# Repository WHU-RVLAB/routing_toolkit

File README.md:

# routing toolkit

## Introduction

## Installation
development installation (direct link to the source code):
```bash
pip install -e .
```
installation (build packege and install it to python site-packages):
```bash
pip install .
```

## Running
routing pcb from kicad:
```bash
python src/rtools/main.py [--kicad_pcb <filepath>] [--kicad_pro <filepath>] [--save_file <filename>]
```

## Thanks to
Code used in this project is based on the following repositories: 

### Parser:
- https://github.com/mvnmgrx/kiutils

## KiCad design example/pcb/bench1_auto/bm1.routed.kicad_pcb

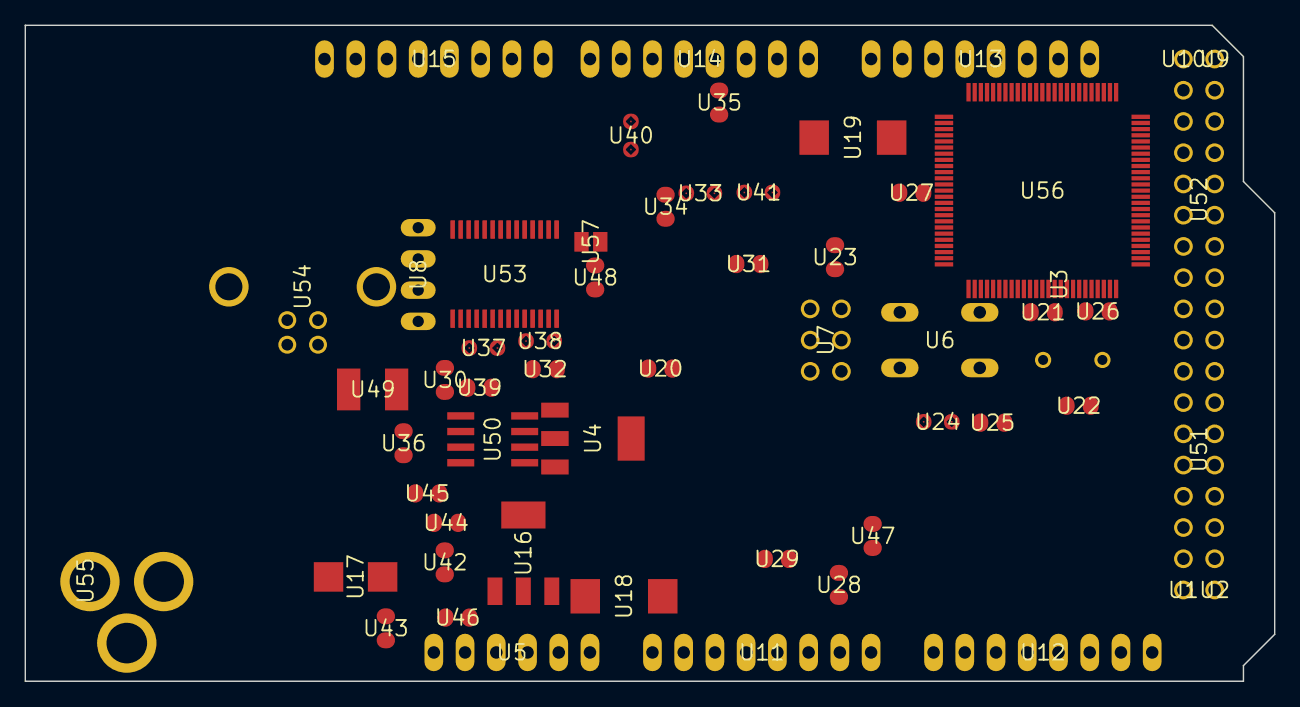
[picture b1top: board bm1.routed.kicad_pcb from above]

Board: 2 copper layers, 101.6 x 53.3 mm, 57 parts (0 on the bottom side), 99 nets, no tracks yet.

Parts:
U1, U2, U9, U10: 1X01
U3: HC49_S
U4, U16: SOT223
U5: 1X06
U6: B3F-10XX
U7: 2X03
U8: JP4
U11, U12, U13, U14, U15: 1X08
U17: SMB
U18, U19: SMC_D
U20, U21, U22, U23, U28, U29, U30, U31, U35, U36, U43, U44, U46, U48: C0805RND
U24, U33, U37, U38: 0805RND
U25, U26, U27, U32, U34, U39, U42, U45, U47: R0805RND
U40, U41: RCL_0805RND
U49: L1812
U50: SO08
U51, U52: 2X08
U53: SSOP28
U54: PN61729
U55: DC-21MM
U56: TQFP100
U57: SJ

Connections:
+3V3: U5.2, U30.2, U50.2, U53.17
+5V: U4.3, U5.3, U7.2, U9.1, U10.1, U16.2, U16.4, U19.+, U20.1, U23.1, U25.1, U26.1, U27.1, U28.1, U29.2, U31.1, U32.2, U39.2, U47.2, U50.8, U53.4, U53.19, U53.20, U56.10, U56.31, U56.61, U56.80, U56.100
ADC0: U11.1, U56.97
ADC1: U11.2, U56.96
ADC2: U11.3, U56.95
ADC3: U11.4, U56.94
ADC4: U11.5, U56.93
ADC5: U11.6, U56.92
ADC6: U11.7, U56.91
ADC7: U11.8, U56.90
ADC8: U12.1, U56.89
ADC9: U12.2, U56.88
ADC10: U12.3, U56.87
ADC11: U12.4, U56.86
ADC12: U12.5, U56.85
ADC13: U12.6, U56.84
ADC14: U12.7, U56.83
ADC15: U12.8, U56.82
AREF: U15.8, U35.1, U56.98
CMP: U42.1, U44.2, U45.2, U50.3
CTS: U8.1, U53.11
D+: U53.15, U54.3
D-: U53.16, U54.2
DCD: U8.3, U53.10
DSR: U8.2, U53.9
DTR: U48.1, U53.2, U57.1, U57.2
GATE_CMD: U4.1, U50.6, U50.7
GND: U1.1, U2.1, U5.4, U5.5, U6.1, U6.2, U7.6, U15.7, U16.1, U18.-, U19.-, U20.2, U21.1, U22.1, U23.2, U24.P$2, U28.2, U29.1, U30.1, U31.2, U33.P$2, U35.2, U36.2, U43.2, U44.1, U45.1, U46.2, U50.4, U53.7, U53.18, U53.21, U53.25, U53.26, U54.4, U54.P$1, U54.P$2, U55.1, U55.3, U56.11, U56.32, U56.62, U56.81, U56.99
M8RXD: U40.P$1, U53.1
M8TXD: U41.P$1, U53.5
unnamed: U33.P$1, U34.2
unnamed: U24.P$1, U25.2
unnamed: U50.1, U50.5
unnamed: U3.1, U21.2, U56.34
unnamed: U3.2, U22.2, U56.33
unnamed: U38.P$2, U53.23
unnamed: U37.P$2, U53.22
unnamed: U32.1, U38.P$1
unnamed: U37.P$1, U39.1
unnamed: U49.2, U54.1
PA0: U52.16, U56.78
PA1: U52.15, U56.77
PA2: U52.14, U56.76
PA3: U52.13, U56.75
PA4: U52.12, U56.74
PA5: U52.11, U56.73
PA6: U52.10, U56.72
PA7: U52.9, U56.71
PB0: U51.1, U56.19
PB1: U7.3, U51.2, U56.20
PB2: U7.4, U51.3, U56.21
PB3: U7.1, U51.4, U56.22
PB4: U15.3, U56.23
PB5: U15.4, U56.24
PB6: U15.5, U56.25
PB7: U15.6, U34.1, U56.26
PC0: U52.1, U56.53
PC1: U52.2, U56.54
PC2: U52.3, U56.55
PC3: U52.4, U56.56
PC4: U52.5, U56.57
PC5: U52.6, U56.58
PC6: U52.7, U56.59
PC7: U52.8, U56.60
PD7: U51.16, U56.50
PE0: U14.1, U40.P$2, U56.2
PE1: U14.2, U41.P$2, U56.3
PE3: U14.6, U56.5
PE4: U14.3, U56.6
PE5: U14.4, U56.7
PG0: U51.13, U56.51
PG1: U51.14, U56.52
PG2: U51.15, U56.70
PG5: U14.5, U56.1
PH3: U14.7, U56.15
PH4: U14.8, U56.16
PH5: U15.1, U56.17
PH6: U15.2, U56.18
PL0: U51.5, U56.35
PL1: U51.6, U56.36
PL2: U51.7, U56.37
PL3: U51.8, U56.38
PL4: U51.9, U56.39
PL5: U51.10, U56.40
PL6: U51.11, U56.41
PL7: U51.12, U56.42
PWRIN: U17.A, U55.2
RESET: U5.1, U6.3, U6.4, U7.5, U46.1, U47.1, U48.2, U56.30
RI: U8.4, U53.6
RXD1: U13.3, U56.45
RXD2: U13.5, U56.12
RXD3: U13.7, U56.63
SCL: U13.1, U26.2, U56.43
SDA: U13.2, U27.2, U56.44
TXD1: U13.4, U56.46
TXD2: U13.6, U56.13
TXD3: U13.8, U56.64
USBVCC: U4.2, U36.1, U49.1
VIN: U5.6, U16.3, U17.C, U18.+, U42.2, U43.1

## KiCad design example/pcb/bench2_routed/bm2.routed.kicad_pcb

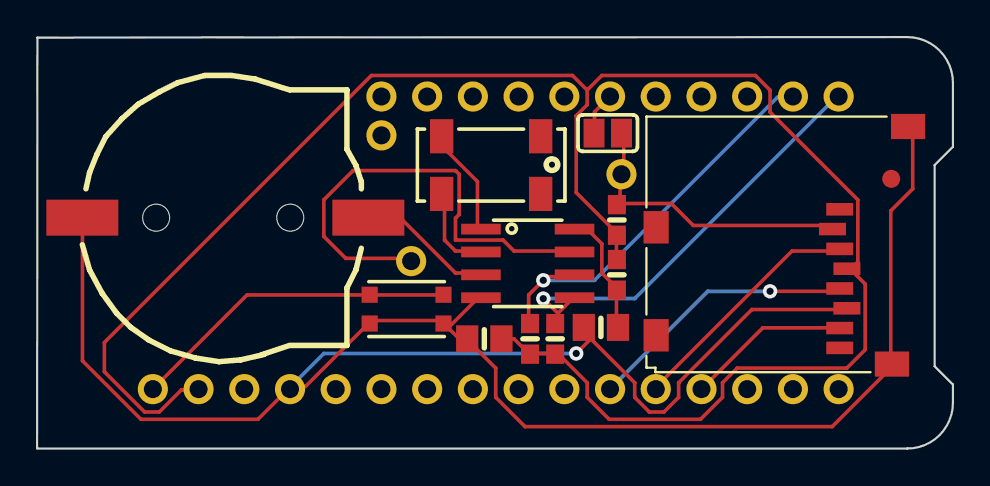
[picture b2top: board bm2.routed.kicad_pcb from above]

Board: 2 copper layers, 50.9 x 22.9 mm, 18 parts (0 on the bottom side), 15 nets.

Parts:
B1: cr1220; CR1220-2
C1, C2: 10uF; 0805-NO
FID1: FIDUCIAL_1MM
IC1: PCF8523T; SOIC8_150MIL
INT1: 1X01_ROUND
JP1: 1X11_ROUND
JP2: 1X16_ROUND
JP3: 1X01_ROUND
R1, R2: 10K; 0603-NO
R3: 100K; 0603-NO
R4: 1K; 0603-NO
SDCS: 1X01_ROUND
SJ1: SOLDERJUMPER_CLOSEDWIRE
SW1: KMR2; BTN_KMR2_4.6X2.8
X4: microsd; MICROSD
Y1: 32khz; CRYSTAL_8X3.8

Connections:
+3V3: C2.1, JP2.15, R1.2, R2.2, R3.2, R4.1, X4.4
CR1220: B1.+, IC1.3
CS: JP1.6, SJ1.1
GND: B1.-, C1.2, C2.2, IC1.4, JP2.13, SW1.A, SW1.A', X4.6, X4.MT1, X4.MT2
INT1: IC1.7, INT1.1
MISO: JP2.4, X4.7
MOSI: JP2.5, X4.3
unnamed: C1.1, IC1.8, R4.2
unnamed: IC1.1, Y1.P$4
unnamed: IC1.2, Y1.P$1
RESET: JP2.16, SW1.B, SW1.B'
SCK: JP2.6, X4.5
SCL: IC1.6, JP1.10, R2.1
SDA: IC1.5, JP1.11, R1.1
SD_CS: R3.1, SDCS.1, SJ1.2, X4.2

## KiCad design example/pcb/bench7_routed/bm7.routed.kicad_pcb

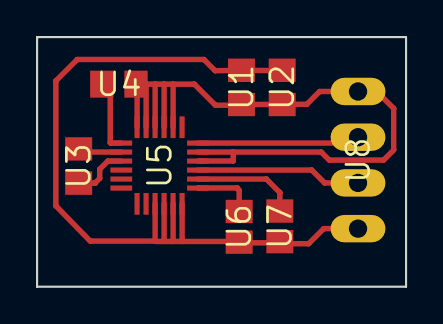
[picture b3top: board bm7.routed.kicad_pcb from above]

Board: 2 copper layers, 20.5 x 13.9 mm, 8 parts (0 on the bottom side), 9 nets.

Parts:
U1, U2, U3, U4: C0805
U5: LGA-24
U6, U7: R0805
U8: MA04-1

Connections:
/SCL: U5.21, U8.2
/SDA: U5.24, U8.3
GND: U1.2, U2.2, U4.1, U5.2, U5.3, U5.4, U5.5, U5.6, U5.22, U5.23, U8.4
unnamed: U3.1, U5.9
unnamed: U3.2, U5.8
unnamed: U4.2, U5.7
unnamed: U5.19, U6.1
unnamed: U5.20, U7.1
VDD: U1.1, U2.1, U5.15, U5.16, U5.17, U5.18, U6.2, U7.2, U8.1

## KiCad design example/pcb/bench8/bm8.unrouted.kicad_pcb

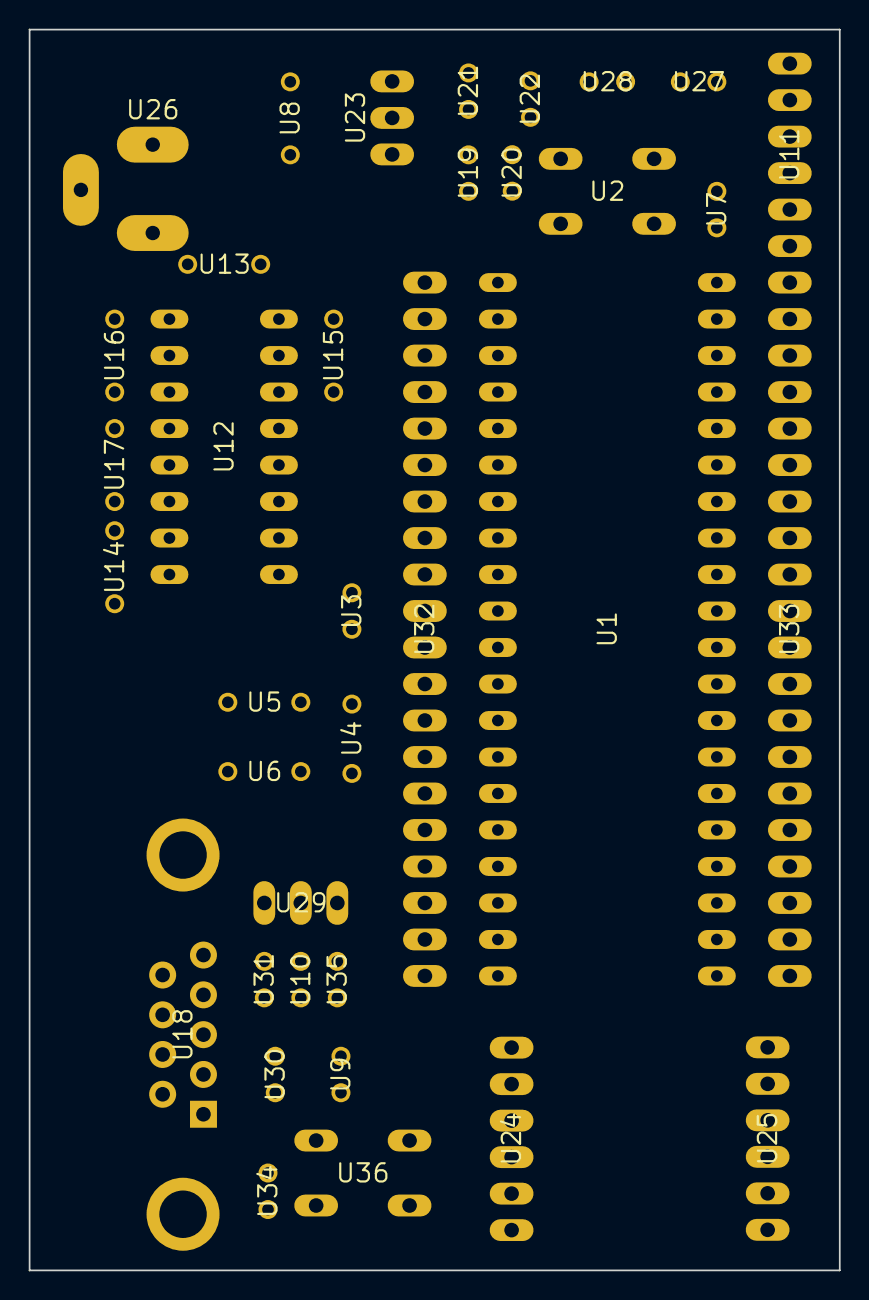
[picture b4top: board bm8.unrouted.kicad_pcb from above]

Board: 2 copper layers, 56.4 x 86.4 mm, 36 parts (0 on the bottom side), 58 nets, no tracks yet.

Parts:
U1: DIL40
U2, U36: B3F-10XX
U3, U22: C025-024X044
U4: HC49_S
U5, U6, U13, U14, U15, U16, U17: C050-024X044
U7, U10, U19, U20, U21, U28, U31, U34, U35: V526-0
U8: C050-025X075
U9, U27, U30: LED3MM
U11, U24, U25: 1X06
U12: DIL16
U18: DB9
U23: 317TS
U26: 733980-62
U29: MA03-1
U32, U33: MA20-1

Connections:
/3.3V_SRC: U1.11, U1.32, U3.1, U7.1, U11.2, U12.16, U13.2, U15.1, U21.2, U22.1, U23.2, U24.3, U28.1, U32.10, U33.9, U36.1
/MRF_CS: U1.17, U24.5, U32.4
/MRF_INT: U1.34, U25.3, U33.7
/MRF_RESET: U1.15, U25.5, U32.6
/MRF_SCK: U1.18, U25.1, U32.3
/MRF_SDI: U1.23, U24.6, U33.18
/MRF_SDO: U1.24, U25.2, U33.17
/MRF_WAKE: U1.16, U25.4, U32.5
/N$17: U1.26, U12.9, U33.15
/N$21: U1.25, U12.10, U33.16
/OS1: U1.13, U4.1, U5.1, U32.8
/OSC2: U1.14, U4.2, U6.1, U32.7
GND: U1.12, U1.31, U2.1, U3.2, U5.2, U6.2, U8.2, U9.K, U11.3, U12.15, U14.1, U15.2, U18.5, U20.1, U22.2, U24.1, U24.2, U25.6, U26.1, U27.K, U30.K, U32.9, U33.10, U34.2
unnamed: U12.2, U13.1
unnamed: U12.6, U14.2
unnamed: U12.1, U16.1
unnamed: U12.3, U16.2
unnamed: U12.4, U17.1
unnamed: U12.5, U17.2
unnamed: U8.1, U23.3, U26.2
unnamed: U12.7, U18.2
unnamed: U12.8, U18.3
unnamed: U1.1, U2.3, U7.2, U11.1, U32.20
unnamed: U1.2, U32.19
unnamed: U1.3, U32.18
unnamed: U1.4, U32.17
unnamed: U1.5, U32.16
unnamed: U1.6, U32.15
unnamed: U1.7, U32.14
unnamed: U1.8, U32.13
unnamed: U1.9, U32.12
unnamed: U1.10, U32.11
unnamed: U1.19, U32.2
unnamed: U1.20, U32.1
unnamed: U1.21, U33.20
unnamed: U1.22, U33.19
unnamed: U1.27, U33.14
unnamed: U1.28, U33.13
unnamed: U1.29, U33.12
unnamed: U1.30, U33.11
unnamed: U1.33, U33.8
unnamed: U1.35, U33.6
unnamed: U1.36, U33.5
unnamed: U1.37, U33.4
unnamed: U1.38, U33.3
unnamed: U1.39, U11.5, U33.2
unnamed: U1.40, U11.4, U33.1
unnamed: U19.2, U21.1, U23.1
unnamed: U27.A, U28.2
unnamed: U30.A, U31.2
unnamed: U9.A, U10.2
unnamed: U34.1, U35.2, U36.3
unnamed: U29.3, U35.1
unnamed: U10.1, U29.2
unnamed: U29.1, U31.1
unnamed: U19.1, U20.2
unnamed: U18.1, U18.4, U18.6
unnamed: U18.7, U18.8

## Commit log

2023-10-26 upload file
2023-10-26 fix (#2)
2023-10-27 refactor code of router
2023-10-27 refactor code of router (#3)
    * refactor code of router
    * update README.md
2023-10-27 add routing layer factor in f_score
2023-10-31 add net ignore & can read trace items and generate them to the grid environment
2023-10-31 When the next node violate DRC, it can not be expended. Now router can rip-up and reroute, but according to the expend logic, it will have no effect.
2023-11-01 add net ignore & read trace items (#5)
    * add net ignore & can read trace items and generate them to the grid environment
    * When the next node violate DRC, it can not be expended.
    Now router can rip-up and reroute, but according to the expend logic, it will have no effect.
2023-11-02 fix the bug of trace width
